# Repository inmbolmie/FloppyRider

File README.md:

# FloppyRider
Disk interface adapter to connect an IBM 31SD or 51TD 8-inch disk unit to a standard PC floppy controller

__This project is currently in Beta stage.__

__Second revision (20220624): I have added a transistor to drive the write/erase-gate signals on the IBM drive. I have noticed that write/erase-gate have a very low input impedance (90 ohms each, could that be a safety measure to make harder to accidentally drive the signal high?) that is way over-spec for the 74LS logic to drive properly. The prototype worked by pure luck but trying with other 74LS components the signal level was too low to enable the gates so the device was only capable of reading. The solution is to include a transistor to drive that signals up to aceptable levels.__

## Introduction

This is an ongoing project to create an adapter to be able to use IBM 8-inch Diskette drives with a standard PC floppy controller.

I currently have a working prototype capable of reading, writing and formatting Diskette 1,2 (SD) and 2D (DD) types on a 51TD disk drive. Further testing will be needed to consider it stable and fully operational.

## Videos

Video showing the adapter in action, here it is used to make an 8-inch diskette MSDOS-bootable:

[Booting MSDOS from an IBM 51TD 8-inch drive](https://www.youtube.com/watch?v=TbLUqG_d6FU)

Using the adapter to image a 33FD-formatted diskette with Imagedisk:

[Imaging on a PC an IBM 8-inch diskette with a 51TD diskette drive, Imagedisk and FloppyRider](https://www.youtube.com/watch?v=4pZ3qMAHVGs)

This project was inspired by CuriousMarc's video about data recovery from 8-inch floppies. This kind of converter is something Master Ken would have made like in five minutes using a Teensy, in case they wanted to use a genuine IBM Diskette drive in their data recovery adventure.

[Fossil Data Part 2: 8-Inch IBM Floppy Data Recovery](https://www.youtube.com/watch?v=5FVwheTVWko)

## Hardware

The adapter hardware is pretty straightforward and can be made cheapily with very low-cost components:

* Pin headers and IDC ribbon cables
* Arduino ProMicro microcontroller board (5V)
* 74LS02
* 74LS06
* 74LS08
* 74LS74
* 12x1K resistors
* 1x4,7K resistor
* NPN transistor

## Software

You can get the Arduino source code for the ProMicro in the __FloppyRider__ directory. You can program it using the regular Arduino IDE.

## KiCad Project

You can get the current project files in the __KiCad__ directory. The PCB design has not been validated at this point.

## Warning about some floppy controllers

It seems that some floppy controllers may ground the signals to the floppy drive when the computer is switched off. If you have a diskettte inserted and engaged when this happens, that can lead to the track where the head is currently positioned to be erased.

If you are working with important media be careful about this, and give power to the 51TD drive only __after__ the computer is switched on, and remove the diskette or the power to the disk drive __before__ the computer is switched off.

## Operation

These are the main points that need to be carried out for conversion:

#### Logic levels

The PC floppy signals are open collector low-level active, while the IBM signals are push-pull high-active. The 74 series chips provide most of the conversion.

All the signals are gated by the "drive select" PC signal for the adapter to be able to operate with another floppy drive on the same cable.

#### Track addressing

The PC floppy adresses tracks by a "direction" and "step" signal, and gets a "track 0" signal when the head is placed at such track. The IBM interface lacks a "track 0" signal and you control direcly the stepper motor signals "access 0" and "access 1". The ProMicro initializes the head position at track 0 at startup. From there it gets track of where the head is actually positioned and translates the required signals on both sides.

#### Write data signal.

The PC floppy write data signal generates a full pulse (falling and rising edge) for each magnetic flux transition that needs to be recorded on the disk surface, while in the IBM interface the "write data" signal records a magnetic flux transition for each signal level change (rising or falling edge). The conversion is made via the 74LS74 flip-flop.

## Connection

The 31SD and 51TD disk drives have pretty hefty power requirements, as you will need to provide them with:

* AC mains power for the disk rotating motor (on a separate connector)
* +24V at 12W (on the 36-pin idc connector)
* +5V (on the 36-pin idc connector)
* -5V (on the 36-pin idc connector)

The easier way to get all the required power rails is getting them from the original host hardware where the disk drive is enclosed. For that reason a 36-pin host connector header is provided. Note that the connector sides are mirrored to be able to use it with a cable-to-cable connection. The adapter will be placed as a bridge between the host cable and the disk drive header.

If you have a separated power supply capable of providing the required DC levels you can leave the host header unconnected and provide power via a separate connector. That way something like a separated disk enclosure could be made.

The other 36-pin header will be used with a regular IDC ribbon cable connector to connect it to the disk drive. Note that you won't be _easily_ able to use the most common 40-pin cables as the available space for the connector in the disk drive is very limited.

_As the connectors carry a powerful +24V signal, connector orientation is critical and getting it wrong, reversing or misplacing it could damage your hardware._

On the other end of the adapter you have a 34-pin header for the PC standard floppy cable. The adapter is hard-wired for drive B as most PC floppy drives are.

## Schematics

As currently working on the prototype unit. Subject to further modification

## PCB

Sample of how the actual PCB could be. Not validated in production examples.

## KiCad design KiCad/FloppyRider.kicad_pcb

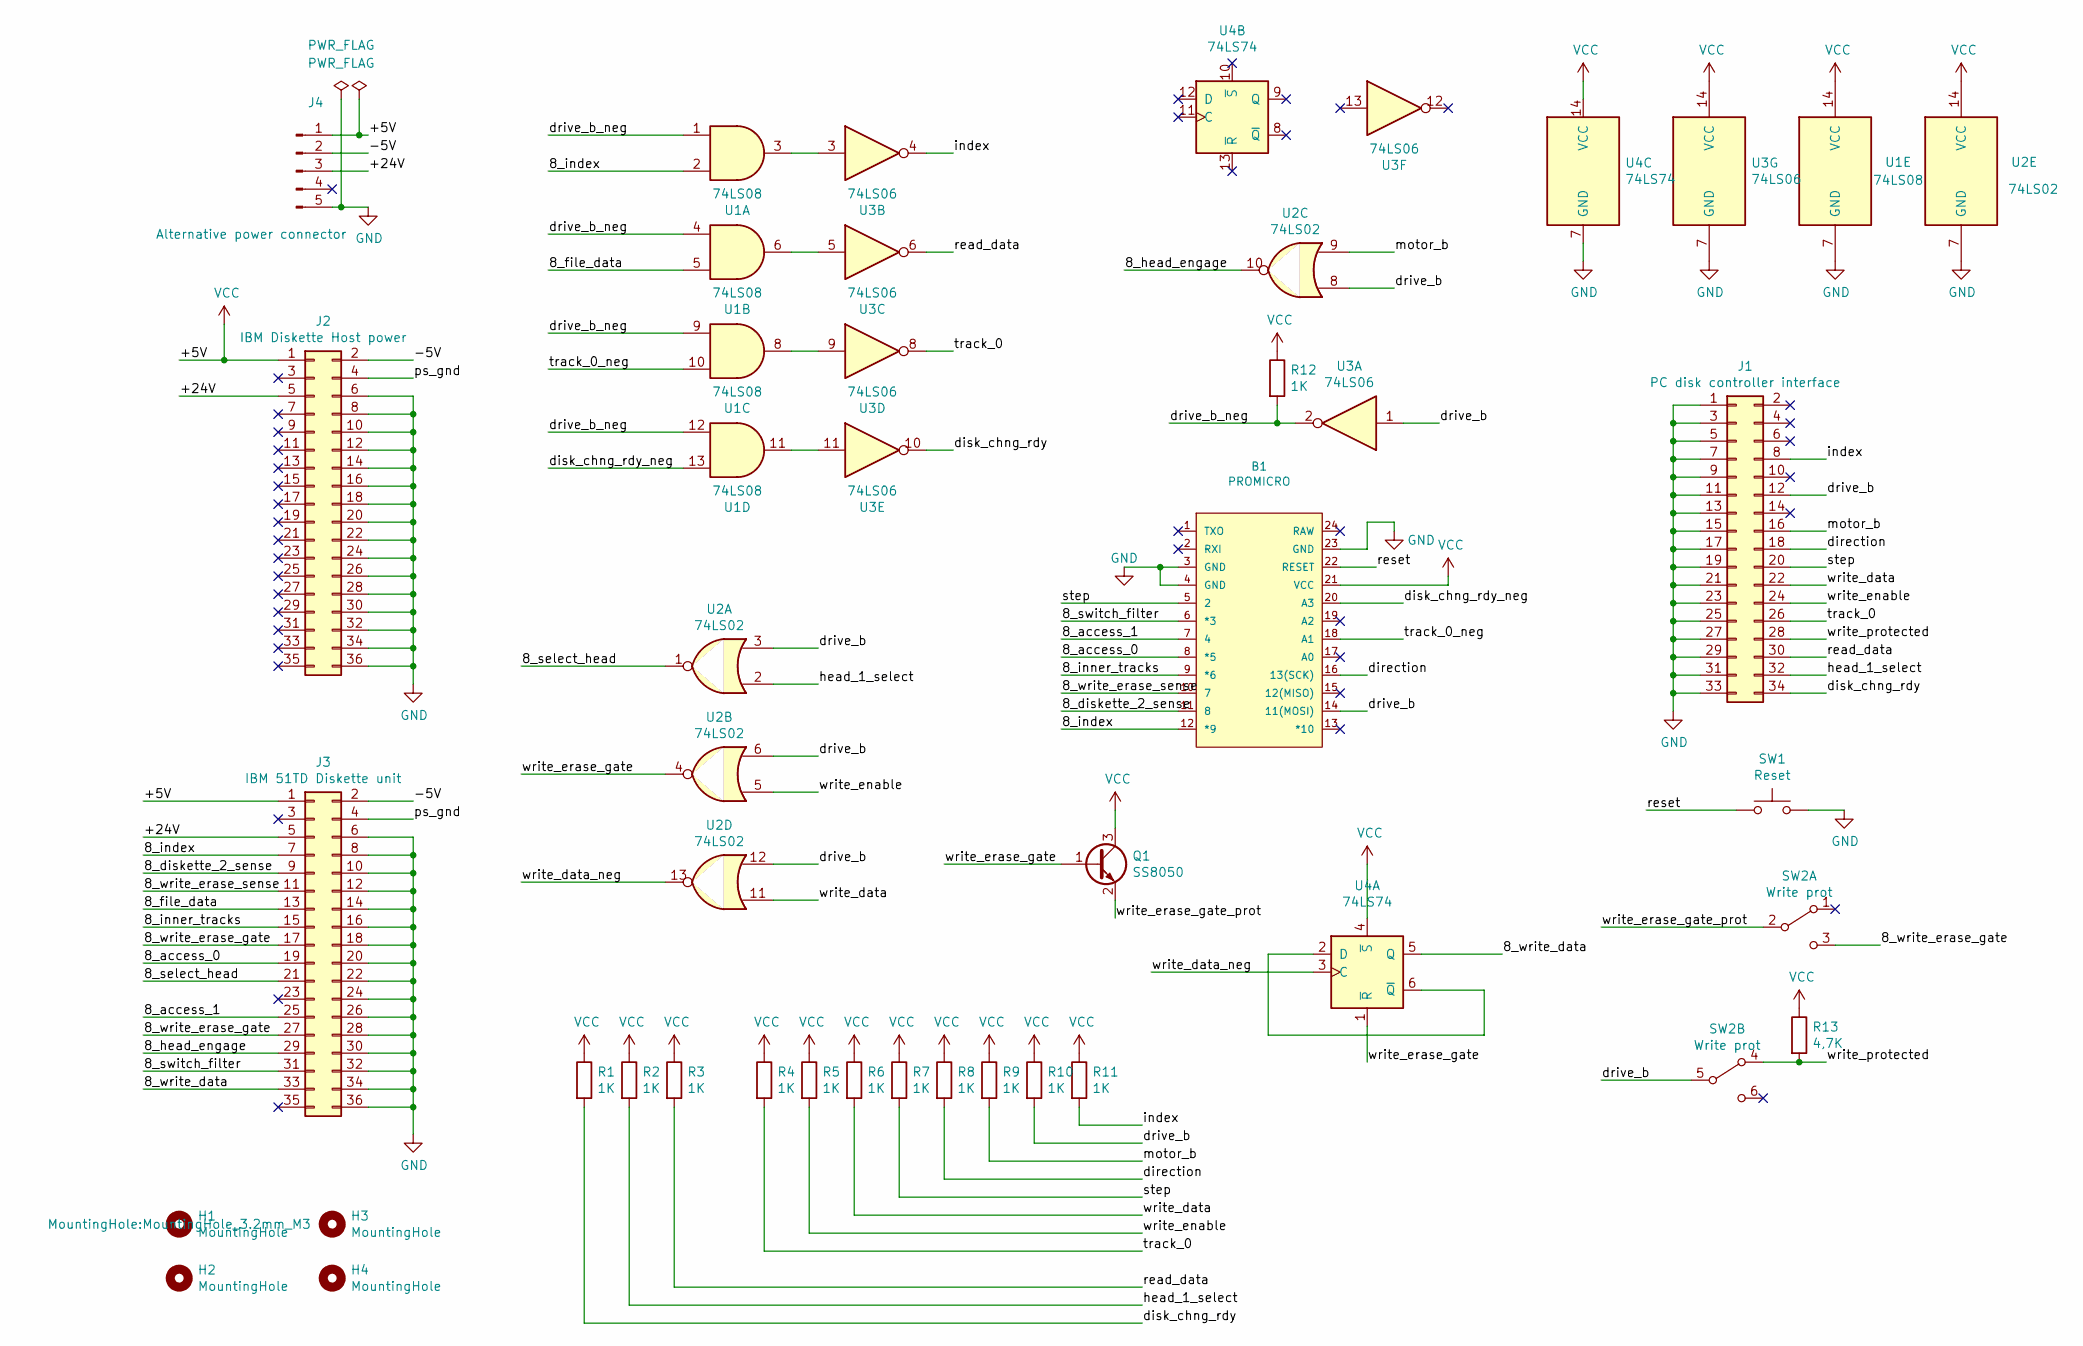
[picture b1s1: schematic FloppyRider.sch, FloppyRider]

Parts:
B1: PROMICRO; SPARKFUN_PRO_MICRO
H1, H2, H3, H4: MountingHole; MountingHole_3.2mm_M3
J1: PC disk controller interface; PinHeader_2x17_P2.54mm_Vertical
J2: IBM Diskette Host power; PinHeader_2x18_P2.54mm_Vertical
J3: IBM 51TD Diskette unit; PinHeader_2x18_P2.54mm_Vertical
J4: Alternative power connector; PinHeader_1x05_P2.54mm_Vertical
Q1: SS8050; SOT-23; LCSC C2150
R1, R2, R3, R4, R5, R6, R7, R8, R9, R10, R11, R12: 1K; R_0603_1608Metric; LCSC C21190
R13: 4,7K; R_0603_1608Metric; LCSC C23162
SW1: Reset; SW_Push_1P1T_NO_6x6mm_H9.5mm; LCSC C221880
SW2: Write prot; SW-TH_K3-2235S-K1
U1: 74LS08; SO-14_3.9x8.65mm_P1.27mm
U2: 74LS02; SO-14_3.9x8.65mm_P1.27mm
U3: 74LS06; SO-14_3.9x8.65mm_P1.27mm; LCSC C113682
U4: 74LS74; SO-14_3.9x8.65mm_P1.27mm; LCSC C39990

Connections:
/8_access_0: B1.8 (*5), J3.19
/8_access_1: B1.7 (4), J3.25
/8_diskette_2_sense: B1.11 (8), J3.9
/8_file_data: J3.13, U1.5
/8_head_engage: J3.29, U2.10
/8_index: B1.12 (*9), J3.7, U1.2
/8_inner_tracks: B1.9 (*6), J3.15
/8_select_head: J3.21, U2.1
/8_switch_filter: B1.6 (*3), J3.31
/8_write_data: J3.33, U4.5 (Q)
/8_write_erase_gate: J3.17, J3.27, SW2.3 (C)
/8_write_erase_sense: B1.10 (7), J3.11
/+24V: J2.5, J3.5, J4.3
/-5V: J2.2, J3.2, J4.2
/direction: B1.16 (13(SCK)), J1.18, R8.2
/disk_chng_rdy: J1.34, R1.2, U3.10
/disk_chng_rdy_neg: B1.20 (A3), U1.13
/drive_b: B1.14 (11(MOSI)), J1.12, R10.2, SW2.5 (B), U2.3, U2.6, U2.8, U2.12, U3.1
/drive_b_neg: R12.2, U1.1, U1.4, U1.9, U1.12, U3.2
/head_1_select: J1.32, R2.2, U2.2
/index: J1.8, R11.2, U3.4
/motor_b: J1.16, R9.2, U2.9
/ps_gnd: J2.4, J3.4
/read_data: J1.30, R3.2, U3.6
/reset: B1.22 (RESET), SW1.1
/step: B1.5 (2), J1.20, R7.2
/track_0: J1.26, R4.2, U3.8
/track_0_neg: B1.18 (A1), U1.10
/write_data: J1.22, R6.2, U2.11
/write_data_neg: U2.13, U4.3 (C)
/write_enable: J1.24, R5.2, U2.5
/write_erase_gate: Q1.1 (B), U2.4, U4.1 (~R)
/write_erase_gate_prot: Q1.2 (E), SW2.2 (B)
/write_protected: J1.28, R13.2, SW2.4 (A)
GND: B1.3 (GND), B1.4 (GND), B1.23 (GND), J1.1, J1.3, J1.5, J1.7, J1.9, J1.11, J1.13, J1.15, J1.17, J1.19, J1.21, J1.23, J1.25, J1.27, J1.29, J1.31, J1.33, J2.6, J2.8, J2.10, J2.12, J2.14, J2.16, J2.18, J2.20, J2.22, J2.24, J2.26, J2.28, J2.30, J2.32, J2.34, J2.36, J3.6, J3.8, J3.10, J3.12, J3.14, J3.16, J3.18, J3.20, J3.22, J3.24, J3.26, J3.28, J3.30, J3.32, J3.34, J3.36, J4.5, SW1.2, U1.7 (GND), U2.7 (GND), U3.7 (GND), U4.7 (GND)
unnamed: U1.3, U3.3
unnamed: U1.6, U3.5
unnamed: U1.8, U3.9
unnamed: U1.11, U3.11
unnamed: U4.2 (D), U4.6 (~Q)
VCC: B1.21 (VCC), J2.1, J3.1, J4.1, Q1.3 (C), R1.1, R2.1, R3.1, R4.1, R5.1, R6.1, R7.1, R8.1, R9.1, R10.1, R11.1, R12.1, R13.1, U1.14 (VCC), U2.14 (VCC), U3.14 (VCC), U4.4 (~S), U4.14 (VCC)

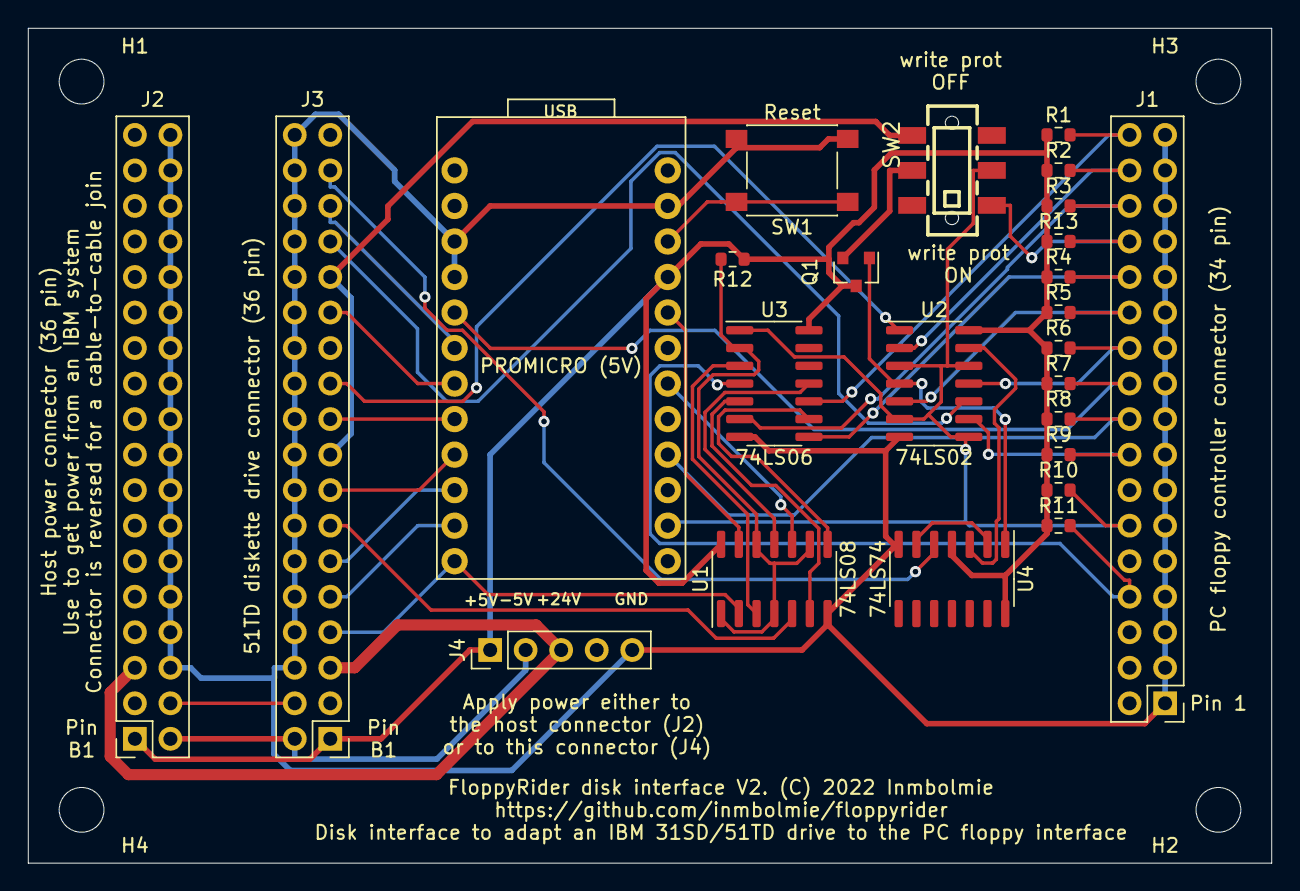
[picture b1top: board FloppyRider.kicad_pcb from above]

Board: 2 copper layers, 88.9 x 59.7 mm, 29 parts (0 on the bottom side), 41 nets.

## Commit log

2022-06-09 Readme
2022-06-09 More readme stuff
2022-06-10 Changes for initial release
2022-06-24 Added transistor to drive write/erase gate signals
2022-06-24 Improved fast track changes
2022-06-24 Revision 2 doc update
2022-06-26 Added hard write protection switch

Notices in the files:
KiCad/FloppyRider.kicad_pcb:
FloppyRider disk interface V2. (C) 2022 Inmbolmie
